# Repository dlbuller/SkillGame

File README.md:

<div align="center">

# SkillGame

**A modern recreation of the 1955 [Bally Skill-Roll](https://www.ipdb.org/machine.cgi?id=4331) coin-roll arcade game** — real coin, real hardware, modern brains.

`ALL HUFF · NO BULL` — WezeBull Games

</div>

---

The player rolls a physical coin up the playfield. It rides the rails, skims the scoring holes, and drops into one to score. Climb the levels without losing the coin to a **gobble hole** — or **tilting** — and you win. A mini-PC runs the whole machine over four FT232H boards and shows the backglass, diagnostics and operator console on a touch monitor.

## Contents

- [How it plays](#how-it-plays) · [Features](#features) · [Screens](#screens) · [Themes](#themes) · [Hardware](#hardware) · [Build the board](#build-the-board) · [Software updates](#software-updates) · [Build &amp; run the app](#build--run-the-app) · [Layout](#layout)

## How it plays

1. **Insert a coin** — a real coin drops through the mech and arms a shot.
2. **Roll it up the playfield.** The coin rides *on top* of the rails and skims across the scoring holes.
3. **Drop it in a hole to score** — `10`–`90`, then the big `100 / 200 / 300 / 400` reels.
4. **Beware the gobble holes.** As you climb into the danger levels the machine flashes its lights and plays a **distract** effect *before* your shot — a real Skill-Roll trick to make you flinch. A miss ends the game.
5. **Land the Winner hole to win.** Tilt the machine too hard and it's game over.

## Features

- 🎯 **Game Status backglass** — live score, level, lamps and the coin animation, driven by the real switch reads.
- 🔧 **Diagnostics** — a live switch map and lamp map, a one-touch **Self-Test** that lights every lamp / pulses the coils / sweeps the LED strip, per-lamp **Identify** blink, and **stuck-switch** detection that turns a tile solid red.
- 📊 **Audits** — plays, wins, hits, high scores and time played, watched over by the auditor gremlin. Demo/attract games are excluded, so the numbers only count real play.
- 🛠️ **Service** — a single-screen operator console for volume, quiet hours, tilt sensitivity and the rest.
- 🎨 **12 themes** — Classy, Fun, Plain, Blackout, Vintage, Maple, Midnight, Synthwave, Lava, Circuit, Galaxy, Ruby; each reskins the whole UI *and* the playfield art. (Settings → Theme)
- ⬆️ **In-app software updates** — checks the WezeBull server, shows the release notes, and installs **any** version forward or back (Service → Check for Updates); it flags new versions on boot. Updates are unzip-and-copy + relaunch — no PC reboot.
- 🗺️ **Interactive schematic page** — a clickable system diagram with crossing-free animated wiring, plus one-tap access to the BOM, fuses, system hookup, full schematic, FT232H pinout and a 3D board viewer.
- 👻 **Attract / demo mode** — with no boards attached the app plays itself, so you can see the whole thing run on a laptop.
- ✅ **56 unit tests** over the game core — scoring, levels, tilt, coin gate, the spring-return lock pulses, stuck detection and the switch router.

## Screens

| | |
|---|---|
| **Schematic** — interactive, clickable system diagram | **Diagnostics** — live switch + lamp maps, self-test |
|  |  |
| **Audits** — plays, wins, hits, high scores (the gremlin) | **Service** — one-page operator console |
|  |  |

## Themes

Pick a look in **Settings → Theme**. Each of the **12 themes** reskins the whole UI *and* the playfield art — and every board below is geometry-matched to the original, so the coin paths never move:

**Classy** (walnut &amp; brass, the default) · **Fun** (arcade neon) · **Plain** (cool slate) · **Blackout** (OLED black &amp; amber) · **Vintage** (the 1949 look) · **Maple** · **Midnight** (navy &amp; chrome) · **Synthwave** · **Lava** · **Circuit** · **Galaxy** · **Ruby** (garnet &amp; gold).

## Hardware

The control board is a custom KiCad 9 design driven by **four Adafruit FT232H** breakouts over USB (MPSSE mode). Everything the software touches maps 1:1 to a real pin.

| Section | What it does |
|---|---|
| **Inputs** | 28 switches on GPIO1–3 (S23 = 7 parallel gobble holes). Commons run on 3.3 V — the FT232H inputs are **not** 5 V-tolerant. |
| **Score lamps** | 16 lamps via PN2222A drivers → 16 off-board **#555 wedge LED bulbs**. |
| **Solenoids** | Coin-Lock + Winner-Lock — **spring-return** coils (plunger out at rest blocks a coin with no power; a brief **pulse** retracts it to drop the coin, never held). TIP120 Darlingtons with 1N4004 flyback, fused (F1/F2 T2A). |
| **LED strip** | 150-pixel WS2812b on GPIO4's SPI line, on its own 5 V feed. |
| **Power** | 3.3 V → J1 (switch commons). One 5 V / 10 A brick splits into two fused branches — **F3** (T3.5A) → J3 (lamps + coils, ~2.7 A) and **F4** (T5A) → the strip's own LED± feed (~3.6 A, firmware brightness-capped). The strip never runs through the board. |

**The lamps are LEDs, wired honestly.** Each score lamp is a non-polar #555 wedge LED bulb in a twist-lock socket. Because the bulb is pre-resistored, the board's lamp positions (R30–R62) are **0 Ω links** — and a 6.3 V bulb on the 5 V rail runs safely under-driven. The **100 / 200 / 300 / 400** holes each drive **two** bulbs in parallel for double brightness.

| Score-lamp bulbs (schematic) | Board (3D) | System hookup |
|---|---|---|
|  |  |  |

## Build the board

Everything you need to source and assemble it is in [`docs/`](docs/):

- 📋 **[Sourced BOM (xlsx)](docs/SkillGame%20BOM%20(sourced).xlsx)** — every part with vendor links + prices (mini-PC, monitor and power included).
- 📖 **[Assembly guide (PDF)](docs/SkillGame%20Assembly%20Guide.pdf)** — an IKEA-style, step-by-step build, parts list on page one.

The KiCad 9 project (schematic + PCB) lives in [`hardware/`](hardware/) — ERC clean and DRC clean.

## Software updates

The machine updates itself over the internet — no USB stick, no reflashing.

**For the operator:** **Service → Check for Updates** lists every published version (newest first, latest tagged). Pick any one to **install forward or roll back** — it shows the release notes, downloads, verifies the file, swaps it in and relaunches. It's unzip-and-copy only: **no PC reboot.** New versions are flagged automatically on boot and every few hours.

**Where it comes from:** releases are hosted free from this repo's [`update/`](https://github.com/dlbuller/SkillGame/tree/main/update) folder over `raw.githubusercontent.com` — [`versions.json`](https://github.com/dlbuller/SkillGame/blob/main/update/versions.json) is the list the app reads. Cut a new version with one command:

```bash
powershell -File tools\publish-update.ps1 -Version 1.1.0 -Notes "What changed."
```

That builds, zips, hashes, writes the manifest + release notes + CHANGELOG, updates the version list, and pushes — the app sees it within a couple of minutes.

## Wiring

Every connector and input is labeled so the board can be wired from the wire side — the labeled board below (and the switch-input pin map + J2 lamp pinout in the guide) show where each wire lands. These are on the app's Schematic page too (**BOARD WIRING** / **INPUT MAP**).

> **Switches:** each hole uses an **arcade coin switch** — a snap-action switch with an 85 mm wire actuator that pokes up through a playfield slot; the rolling coin trips the wire (the long wire gives it a feather-light touch). It mounts hidden under the playfield and wires like any SPDT switch (~$3.99 ea, cheaper in packs).

## Build &amp; run the app

```bash
cd SkillGameWpf
dotnet build -c Debug -p:Platform=x64
```

```bash
cd "SkillGame Source/SkillGame.Tests"
dotnet test
```

The app targets `net8.0-windows` (WPF, x64). With no FT232H boards attached it runs in demo/preview mode, so you can try it on any Windows machine.

## Layout

| Folder | What it is |
|--------|-----------|
| `SkillGameWpf/` | The WPF (.NET 8) front-end / operator console — Game Status, Diagnostics, Settings, Audits, Schematic, Service. |
| `SkillGame Source/SkillGame/` | The UI-agnostic game core (engine, switch map, audits, hardware coordinator). The WPF app links these files directly. |
| `SkillGame Source/SkillGame.Tests/` | xUnit tests for the core. |
| `hardware/` | The KiCad 9 schematic + PCB for the WezeBull Games control board. |
| `docs/` | Sourced BOM, IKEA-style assembly guide, and the schematic-page images. |

## Credits

Scott Wezeman &amp; Dan Bullerman — **WezeBull Games**. *All huff, no bull.*

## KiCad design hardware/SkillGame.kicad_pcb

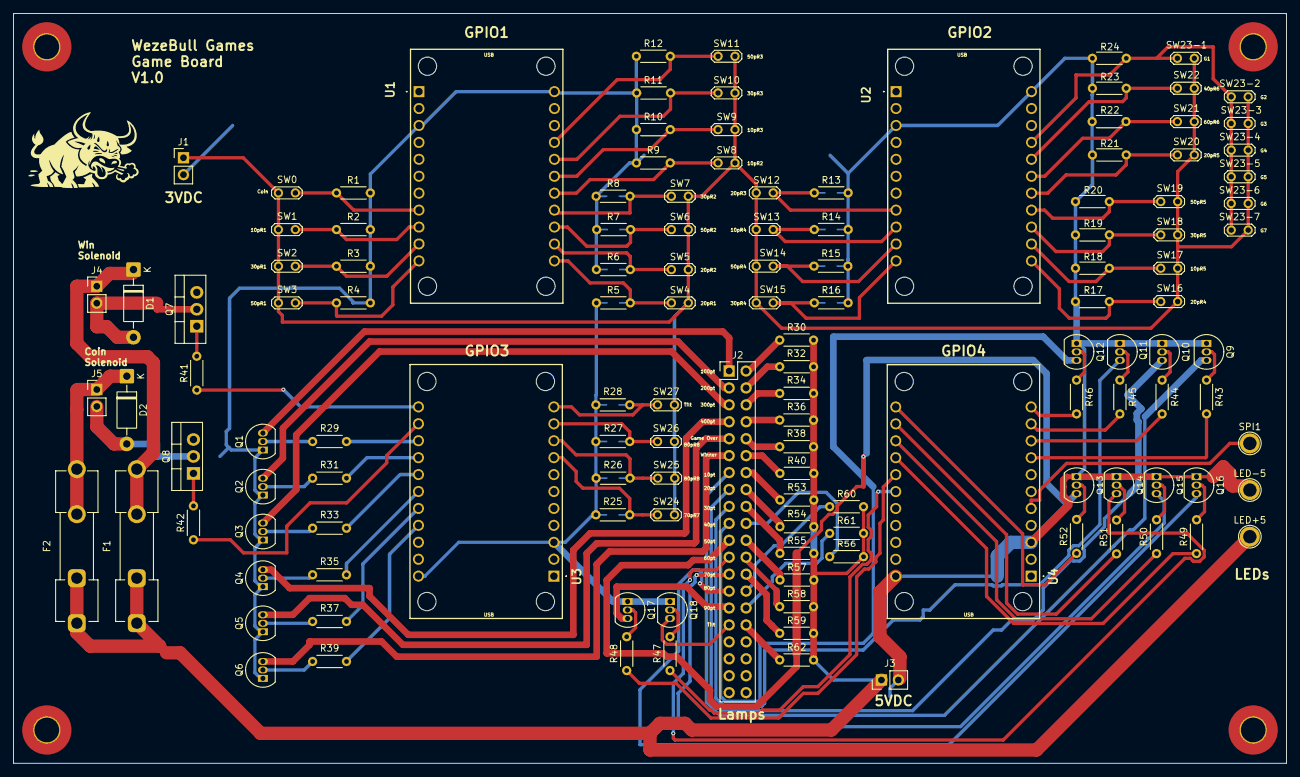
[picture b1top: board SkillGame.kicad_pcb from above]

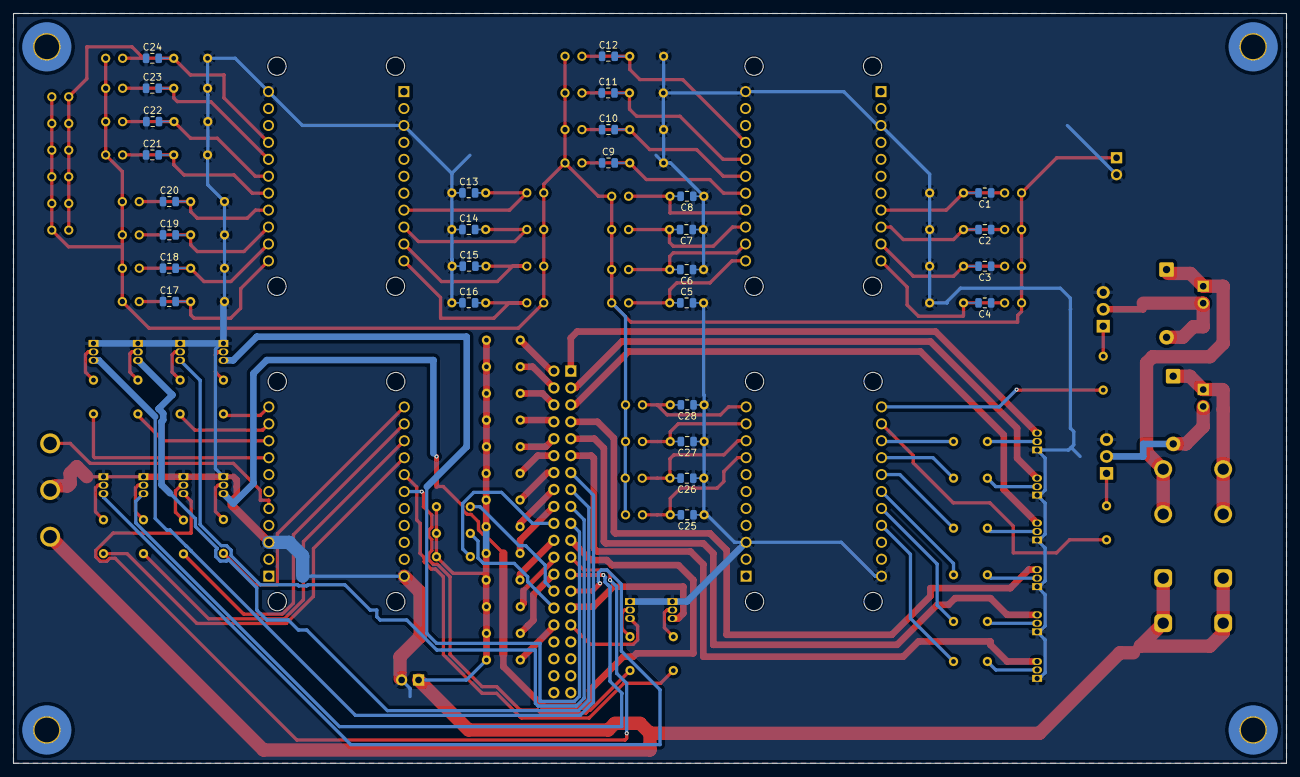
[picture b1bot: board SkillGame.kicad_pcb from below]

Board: 2 copper layers, 191.0 x 112.5 mm, 162 parts (28 on the bottom side), 104 nets.

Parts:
C1, C2, C3, C4, C5, C6, C7, C8, C9, C10, C11, C12, C13, C14, C15, C16, C17, C18, C19, C20, C21, C22, C23, C24, C25, C26, C27, C28: 100nF; C_0805_2012Metric
D1, D2: 1N4004; D_DO-41_SOD81_P10.16mm_Horizontal
F1, F2: Fuse; Fuseholder_Clip-5x20mm_Keystone_3517_Inline_P23.11x6.76mm_D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
H1, H2, H3, H4: MountingHole; MountingHole_3.7mm_Pad_TopBottom
J1, J3, J4, J5: Conn_01x02_Pin; PinHeader_1x02_P2.54mm_Vertical
J2: Conn_02x20_Odd_Even; PinHeader_2x20_P2.54mm_Vertical
LED+5: 5VDC+; TestPoint_Plated_Hole_D2.0mm
LED-5: 5VDC-; TestPoint_Plated_Hole_D2.0mm
Q1, Q2, Q3, Q4, Q5, Q6, Q9, Q10, Q11, Q12, Q13, Q14, Q15, Q16, Q17, Q18: PN2222A; TO-92_Inline
Q7, Q8: TIP120; TO-220-3_Vertical
R1, R2, R3, R4, R5, R6, R7, R8, R9, R10, R11, R12, R13, R14, R15, R16, R17, R18, R19, R20, R21, R22, R23, R24, R25, R26, R27, R28: 10k; R_Axial_DIN0204_L3.6mm_D1.6mm_P5.08mm_Horizontal
R29, R31, R33, R35, R37, R39, R43, R44, R45, R46, R47, R48, R49, R50, R51, R52: 1.00k; R_Axial_DIN0204_L3.6mm_D1.6mm_P5.08mm_Horizontal
R30, R32, R34, R36, R38, R40, R53, R54, R55, R56, R57, R58, R59, R60, R61, R62: 0 R; R_Axial_DIN0204_L3.6mm_D1.6mm_P5.08mm_Horizontal
R41, R42: 2.2k; R_Axial_DIN0204_L3.6mm_D1.6mm_P5.08mm_Horizontal
SPI1: SPI; TestPoint_Plated_Hole_D2.0mm
SW0, SW1, SW2, SW3, SW4, SW5, SW6, SW7, SW8, SW9, SW10, SW11, SW12, SW13, SW14, SW15, SW16, SW17, SW18, SW19, SW20, SW21, SW22, SW23-1, SW23-2, SW23-3, SW23-4, SW23-5, SW23-6, SW23-7, SW24, SW25, SW26, SW27: SW_DPST_x2; TestPoint_2Pads_Pitch2.54mm_Drill0.8mm
U1, U2, U3, U4: Conn_01x11_Socket_FT232H; FT232H_Final

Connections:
GNDREF: C1.1, C2.1, C3.1, C4.1, C5.2, C6.1, C7.1, C8.1, C9.1, C10.1, C11.1, C12.1, C13.1, C14.1, C15.1, C16.1, C17.1, C18.1, C19.1, C20.1, C21.1, C22.1, C23.1, C24.1, C25.1, C26.1, C27.1, C28.1, J1.2, J3.2, LED-5.1, Q1.1 (E), Q2.1 (E), Q3.1 (E), Q4.1 (E), Q5.1 (E), Q6.1 (E), Q7.3 (E), Q8.3 (E), Q9.1 (E), Q10.1 (E), Q11.1 (E), Q12.1 (E), Q13.1 (E), Q14.1 (E), Q15.1 (E), Q16.1 (E), Q17.1 (E), Q18.1 (E), R1.2, R2.2, R3.2, R4.2, R5.2, R6.2, R7.2, R8.2, R9.2, R10.2, R11.2, R12.2, R13.2, R14.2, R15.2, R16.2, R17.2, R18.2, R19.2, R20.2, R21.2, R22.2, R23.2, R24.2, R25.2, R26.2, R27.2, R28.2, U1.3 (GND), U1.22 (GND), U2.3 (GND), U2.22 (GND), U3.3 (GND), U3.22 (GND), U4.3 (GND), U4.22 (GND)
unnamed: D1.2 (A), J4.2, Q7.2 (C)
unnamed: D1.1 (K), F1.2, J4.1
unnamed: D2.2 (A), J5.2, Q8.2 (C)
unnamed: D2.1 (K), F2.2, J5.1
unnamed: J1.1, SW0.1 (A), SW1.1 (A), SW2.1 (A), SW3.1 (A), SW4.1 (A), SW5.1 (A), SW6.1 (A), SW7.1 (A), SW8.1 (A), SW9.1 (A), SW10.1 (A), SW11.1 (A), SW12.1 (A), SW13.1 (A), SW14.1 (A), SW15.1 (A), SW16.1 (A), SW17.1 (A), SW18.1 (A), SW19.1 (A), SW20.1 (A), SW21.1 (A), SW22.1 (A), SW23-1.1 (A), SW23-2.1 (A), SW23-3.1 (A), SW23-4.1 (A), SW23-5.1 (A), SW23-6.1 (A), SW23-7.1 (A), SW24.1 (A), SW25.1 (A), SW26.1 (A), SW27.1 (A)
unnamed: J2.1, Q1.3 (C)
unnamed: J2.2, R30.1
unnamed: J2.3, Q2.3 (C)
unnamed: J2.4, R32.1
unnamed: J2.5, Q3.3 (C)
unnamed: J2.6, R34.1
unnamed: J2.7, Q4.3 (C)
unnamed: J2.8, R36.1
unnamed: J2.9, Q5.3 (C)
unnamed: J2.10, R38.1
unnamed: J2.11, Q6.3 (C)
unnamed: J2.12, R40.1
unnamed: J2.13, Q9.3 (C)
unnamed: J2.14, R53.1
unnamed: J2.15, Q10.3 (C)
unnamed: J2.16, R54.1
unnamed: J2.17, Q11.3 (C)
unnamed: J2.18, R55.1
unnamed: J2.19, Q12.3 (C)
unnamed: J2.20, R56.1
unnamed: J2.21, Q13.3 (C)
unnamed: J2.22, R57.1
unnamed: J2.23, Q14.3 (C)
unnamed: J2.24, R58.1
unnamed: J2.25, Q15.3 (C)
unnamed: J2.26, R59.1
unnamed: J2.27, Q16.3 (C)
unnamed: J2.28, R60.1
unnamed: J2.29, Q17.3 (C)
unnamed: J2.30, R61.1
unnamed: J2.31, Q18.3 (C)
unnamed: J2.32, R62.1
unnamed: F1.1, F2.1, J3.1, LED+5.1, R30.2, R32.2, R34.2, R36.2, R38.2, R40.2, R53.2, R54.2, R55.2, R56.2, R57.2, R58.2, R59.2, R60.2, R61.2, R62.2
unnamed: Q1.2 (B), R29.2
unnamed: Q2.2 (B), R31.2
unnamed: Q3.2 (B), R33.2
unnamed: Q4.2 (B), R35.2
unnamed: Q5.2 (B), R37.2
unnamed: Q6.2 (B), R39.2
unnamed: Q7.1 (B), R41.2
unnamed: Q8.1 (B), R42.2
unnamed: Q9.2 (B), R43.1
unnamed: Q10.2 (B), R44.1
unnamed: Q11.2 (B), R45.1
unnamed: Q12.2 (B), R46.1
unnamed: Q13.2 (B), R52.2
unnamed: Q14.2 (B), R51.2
unnamed: Q15.2 (B), R50.2
unnamed: Q16.2 (B), R49.2
unnamed: Q17.2 (B), R48.2
unnamed: Q18.2 (B), R47.2
unnamed: C1.2, R1.1, SW0.2 (B), U1.8 (D4)
unnamed: C2.2, R2.1, SW1.2 (B), U1.9 (D5)
unnamed: C3.2, R3.1, SW2.2 (B), U1.10 (D6)
unnamed: C4.2, R4.1, SW3.2 (B), U1.11 (D7)
unnamed: C5.1, R5.1, SW4.2 (B), U1.12 (C0)
unnamed: C6.2, R6.1, SW5.2 (B), U1.13 (C1)
unnamed: C7.2, R7.1, SW6.2 (B), U1.14 (C2)
unnamed: C8.2, R8.1, SW7.2 (B), U1.15 (C3)
unnamed: C9.2, R9.1, SW8.2 (B), U1.16 (C4)
unnamed: C10.2, R10.1, SW9.2 (B), U1.17 (C5)
unnamed: C11.2, R11.1, SW10.2 (B), U1.18 (C6)
unnamed: C12.2, R12.1, SW11.2 (B), U1.19 (C7)
unnamed: C13.2, R13.1, SW12.2 (B), U2.8 (D4)
unnamed: C14.2, R14.1, SW13.2 (B), U2.9 (D5)
unnamed: C15.2, R15.1, SW14.2 (B), U2.10 (D6)
unnamed: C16.2, R16.1, SW15.2 (B), U2.11 (D7)
unnamed: C17.2, R17.1, SW16.2 (B), U2.12 (C0)
unnamed: C18.2, R18.1, SW17.2 (B), U2.13 (C1)
unnamed: C19.2, R19.1, SW18.2 (B), U2.14 (C2)
unnamed: C20.2, R20.1, SW19.2 (B), U2.15 (C3)
unnamed: C21.2, R21.1, SW20.2 (B), U2.16 (C4)
unnamed: C22.2, R22.1, SW21.2 (B), U2.17 (C5)
unnamed: C23.2, R23.1, SW22.2 (B), U2.18 (C6)
unnamed: C24.2, R24.1, SW23-1.2 (B), SW23-2.2 (B), SW23-3.2 (B), SW23-4.2 (B), SW23-5.2 (B), SW23-6.2 (B), SW23-7.2 (B), U2.19 (C7)
unnamed: C25.2, R25.1, SW24.2 (B), U3.8 (D4)
unnamed: C26.2, R26.1, SW25.2 (B), U3.9 (D5)
unnamed: C27.2, R27.1, SW26.2 (B), U3.10 (D6)
unnamed: C28.2, R28.1, SW27.2 (B), U3.11 (D7)
unnamed: R41.1, U3.12 (C0)
unnamed: R42.1, U3.13 (C1)
unnamed: R29.1, U3.14 (C2)
unnamed: R31.1, U3.15 (C3)
unnamed: R33.1, U3.16 (C4)
unnamed: R35.1, U3.17 (C5)
unnamed: R37.1, U3.18 (C6)
unnamed: R39.1, U3.19 (C7)
unnamed: R52.1, U4.12 (C0)
unnamed: R51.1, U4.13 (C1)
unnamed: R50.1, U4.14 (C2)
unnamed: R49.1, U4.15 (C3)
unnamed: R48.1, U4.16 (C4)
unnamed: R47.1, U4.17 (C5)
unnamed: SPI1.1, U4.5 (D1)
unnamed: R43.2, U4.8 (D4)
unnamed: R44.2, U4.9 (D5)
unnamed: R45.2, U4.10 (D6)
unnamed: R46.2, U4.11 (D7)
